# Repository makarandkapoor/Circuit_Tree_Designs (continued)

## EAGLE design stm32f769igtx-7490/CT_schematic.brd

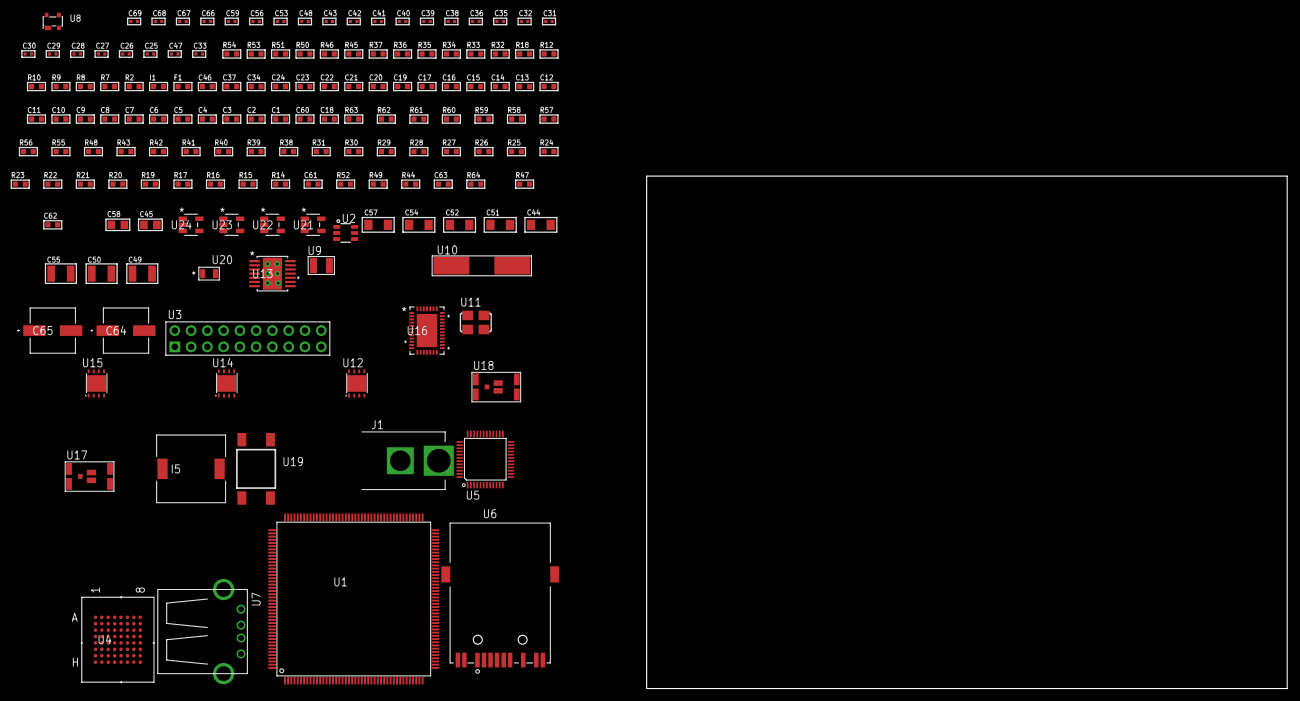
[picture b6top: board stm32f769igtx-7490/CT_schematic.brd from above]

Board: 2 copper layers, 100.0 x 80.0 mm, 154 parts (0 on the bottom side), 146 nets, no tracks yet.

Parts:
C1, C21, C34, C37, C46: 1e-06; C0603
C2, C3, C4, C5, C6, C7, C8, C9, C10, C11, C12, C13, C14, C15, C16, C17, C19, C22, C23, C24: 1e-07; C0603
C18: 4.7e-06; C0603
C20: 1e-08; C0603
C25, C26, C27, C28: 1e-11; C0402
C29, C30, C35, C38, C40, C41, C48, C59: 1e-07; C0402
C31, C32, C36, C39, C42, C43, C53, C56, C66, C67, C68, C69: 1e-08; C0402
C33: 2.2e-08; C0402
C44, C51, C52, C54, C57: 1e-05; C1206
C45, C58: 1e-05; C0805
C47: 3.3e-09; C0402
C49, C50: 2.2e-05; C1210
C55: 1e-05; C1210
C60: 2.2e-06; C0603
C61: 2.45e-08; R0603
C62: 2.8258362168397e-09; R0603
C63: 7.105e-09; R0603
C64, C65: 0.0001; EXV-9H
F1: 240.0; L0603
I1: 97.0; R0603
I5: 3.8e-06; DR1040
J1: PJ-037B; PJ-037B_PACKAGE
R2, R46, R51, R54: 1000.0; R0603
R7, R8, R9, R37: 4700.0; R0603
R10, R12: 2200.0; R0603
R14: 47000.0; R0603
R15, R16, R17, R19, R20, R21, R22, R23, R24, R25, R26, R27, R28, R29, R30, R31, R38, R39, R40, R41, R42, R43, R55, R57, R58, R61, R62, R63: 10000.0; R0603
R18: 1270.0; R0603
R32, R33: 0.1; R0603
R34, R35, R45, R53: 200.0; R0603
R36: 2490.0; R0603
R44, R49, R52: 100000.0; R0603
R47: 71007.101651032; R0603
R48: 22000.0; R0603
R50: 3900.0; R0603
R56: 75000.0; R0603
R59, R60: 95300.0; R0603
R64: 85527.272727273; R0603
U1: STM32F769IGT6; LQFP176
U2: MAX4995AAUT+T; SOT-23-6
U3: TST-110-05-T-D-RA
U4: mt28ew512aba1HPC-0AAT; LBGA-64
U5: RTL8201FL-VB-CG
U6: 7498011122R
U7: 61400416021; USB-A-H
U8: prtr5v0u2ax; SOT143B
U9: ABS07-32.768KHZ-7-T
U10: ABLS-25.000MHZ-B2F-T
U11: ASFL1-25MHZ-NCS; ASFL1
U12, U14, U15: LP3878SDX-ADJ/NOPB; WSON-8
U13: tps54325PWP; HTSSOP14
U16: LTC2928CUHF#PBF; QFN-38_UHF
U17, U18: IRF8306MTRPbF; IRF8306MTRPBF
U19: 4-1437565-2; SW_4-1437565-2
U20: Q65110A2395; LGM67K-G1J2-24-Z
U21, U22, U23, U24: nc7sz125m5x; NC7SZ125M5X

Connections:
CLK_CRYSTAL_U1_9: C25.1, U1.9, U9.1
CLK_CRYSTAL_U1_10: C26.1, U1.10, U9.2
CLK_CRYSTAL_U1_29: C27.1, U1.29, U10.1
CLK_CRYSTAL_U1_30: C28.1, U1.30, U10.2
CLK_U5_43: U5.43, U11.3
GND: C1.2, C2.2, C3.2, C4.2, C5.2, C6.2, C7.2, C8.2, C9.2, C10.2, C11.2, C12.2, C13.2, C14.2, C15.2, C16.2, C17.2, C18.2, C19.2, C20.2, C21.2, C22.2, C23.2, C24.2, C25.2, C26.2, C27.2, C28.2, C29.2, C30.2, C31.2, C32.2, C33.2, C34.2, C35.2, C36.2, C37.2, C38.2, C39.2, C40.2, C41.2, C42.2, C43.2, C44.2, C45.2, C46.2, C47.2, C49.2, C50.2, C51.2, C52.2, C53.2, C54.2, C55.2, C56.2, C57.2, C58.2, C59.2, C60.2, C61.2, C62.2, C63.2, C64.2, C65.2, C66.2, C67.2, C68.2, C69.2, J1.2, R2.2, R14.2, R15.2, R18.2, R20.2, R26.2, R32.2, R33.2, R36.2, R38.2, R40.2, R41.2, R42.2, R46.2, R48.2, R51.2, R54.2, R56.2, R59.2, R60.2, R61.2, R62.2, R63.2, U1.14, U1.22, U1.37, U1.61, U1.71, U1.95, U1.103, U1.109, U1.117, U1.130, U1.135, U1.148, U1.158, U2.2, U3.4, U3.6, U3.8, U3.10, U3.12, U3.14, U3.16, U3.18, U3.20, U4.E8, U4.H2, U4.H7, U5.7, U5.20, U5.33, U5.42, U5.47, U6.11, U7.4, U7.5, U7.6, U8.1, U11.2, U12.3, U12.PAD, U13.5, U13.8, U13.9, U13.15, U14.3, U14.PAD, U15.3, U15.PAD, U16.8, U16.9, U16.10, U16.12, U16.13, U16.24, U16.25, U16.30, U16.32, U16.39, U20.C, U21.2, U21.3, U22.1, U22.3, U23.1, U23.3, U24.1, U24.3
NET_U1_31: R9.1, U1.31, U24.4
NET_U1_33: R10.1, U1.33, U5.30
NET_U1_39: C20.1, C21.1, F1.1, U1.38, U1.39
NET_U1_42: R12.1, U1.42, U5.31
NET_U1_48: R17.1, U1.48
NET_U1_125: R18.1, U1.125
NET_U1_129: C24.1, U1.129
NET_U1_166: R15.1, U1.166
NET_U1_171: R16.1, U1.171
NET_U1_176: U19.3, U19.4
NET_U2_3: R14.1, U2.3
NET_U3_19: R26.1, U3.19
NET_U4_B4: R30.1, U4.B4
NET_U4_B5: R8.1, U4.B5, U23.4
NET_U5_6: C34.1, C35.1, C36.1, I1.1, U5.6, U5.41
NET_U5_10: R41.1, U5.10
NET_U5_29: R7.1, U5.29, U22.4
NET_U5_32: R37.1, U5.32
NET_U5_34: R39.1, U5.34
NET_U5_35: R40.1, U5.35
NET_U5_40: C41.1, U5.40
NET_U5_46: R36.1, U5.46
NET_U5_48: C40.1, U5.48
NET_U6_1: U5.1, U6.1
NET_U6_3: U5.2, U6.3
NET_U6_4: U5.4, U6.4
NET_U6_5: C33.1, U6.2, U6.5
NET_U6_6: U5.5, U6.6
NET_U6_8: R33.1, U6.8
NET_U6_10: R34.1, U6.10
NET_U6_12: R35.1, U6.12
NET_U6_13: R32.1, U6.13, U6.14
NET_U12_1: C43.1, U12.1
NET_U12_6: R45.2, R46.1, U12.6
NET_U12_8: R44.1, U12.8
NET_U13_2: R47.2, R48.1, U13.2
NET_U13_3: C46.1, U13.3
NET_U13_4: C47.1, U13.4
NET_U13_10: C48.1, I5.1, U13.10, U13.11
NET_U13_12: C48.2, U13.12
NET_U14_1: C53.1, U14.1
NET_U14_6: R50.2, R51.1, U14.6
NET_U14_8: R49.1, U14.8
NET_U15_1: C56.1, U15.1
NET_U15_6: R53.2, R54.1, U15.6
NET_U15_8: R52.1, U15.8
NET_U16_3: R62.1, U16.3
NET_U16_6: R59.1, U16.6
NET_U16_7: R60.1, U16.7
NET_U16_16: R61.1, R64.1, U16.16
NET_U16_18: R58.1, U16.18
NET_U16_19: R57.1, U16.19, U16.20
NET_U16_21: R55.1, R56.1, U16.21, U21.4, U22.2, U23.2, U24.2
NET_U16_22: C59.1, R55.2, R57.2, R58.2, U16.11, U16.22
NET_U16_26: C62.1, U16.26
NET_U16_27: C61.1, U16.27
NET_U16_28: C63.1, U16.28
NET_U16_38: R63.1, U16.38
NET_U17_3: U16.2, U17.3
NET_U18_3: U16.37, U18.3
NET_U19_1: R2.1, U19.1, U19.2
PROC_ETH_COL: U1.44, U5.38
PROC_ETH_CRS: U1.43, U5.36
PROC_ETH_RXD0: U1.54, U5.14
PROC_ETH_RXD1: U1.55, U5.16
PROC_ETH_RXD2: U1.56, U5.17
PROC_ETH_RXD3: R42.1, U1.57, U5.18
PROC_ETH_RX_CLK: U1.41, U5.19
PROC_ETH_RX_DV: R38.1, U1.53, U5.13
PROC_ETH_RX_ER: R43.1, U1.12, U5.39
PROC_ETH_TXD0: U1.85, U5.23
PROC_ETH_TXD1: U1.86, U5.24
PROC_ETH_TXD2: U1.34, U5.25
PROC_ETH_TXD3: U1.167, U5.26
PROC_ETH_TX_CLK: U1.35, U5.22
PROC_ETH_TX_EN: U1.80, U5.27
PROC_FMC_A0: U1.16, U4.E2
PROC_FMC_A1: U1.17, U4.D2
PROC_FMC_A2: U1.18, U4.C2
PROC_FMC_A3: U1.19, U4.A2
PROC_FMC_A4: U1.20, U4.B2
PROC_FMC_A5: U1.21, U4.D3
PROC_FMC_A6: U1.60, U4.C3
PROC_FMC_A7: U1.63, U4.A3
PROC_FMC_A8: U1.64, U4.B6
PROC_FMC_A9: U1.65, U4.A6
PROC_FMC_A10: U1.66, U4.C6
PROC_FMC_A11: U1.67, U4.D6
PROC_FMC_A12: U1.110, U4.B7
PROC_FMC_A13: U1.111, U4.A7
PROC_FMC_A14: U1.112, U4.C7
PROC_FMC_A15: U1.113, U4.D7
PROC_FMC_A16: U1.92, U4.E7
PROC_FMC_A17: U1.93, U4.B3
PROC_FMC_A18: U1.94, U4.C4
PROC_FMC_A19: U1.2, U4.D5
PROC_FMC_A20: U1.3, U4.D4
PROC_FMC_A21: U1.4, U4.C5
PROC_FMC_A22: U1.5, U4.B8
PROC_FMC_A23: U1.1, U4.C8
PROC_FMC_A24: U1.156, U4.F8
PROC_FMC_D0: U1.97, U4.E3
PROC_FMC_D1: U1.98, U4.H3
PROC_FMC_D2: U1.142, U4.E4
PROC_FMC_D3: U1.143, U4.H4
PROC_FMC_D4: U1.68, U4.H5
PROC_FMC_D5: U1.69, U4.E5
PROC_FMC_D6: U1.70, U4.H6
PROC_FMC_D7: U1.73, U4.E6
PROC_FMC_D8: U1.74, U4.F3
PROC_FMC_D9: U1.75, U4.G3
PROC_FMC_D10: U1.76, U4.F4
PROC_FMC_D11: U1.77, U4.G4
PROC_FMC_D12: U1.78, U4.F5
PROC_FMC_D13: U1.89, U4.G6
PROC_FMC_D14: U1.90, U4.F6
PROC_FMC_D15: U1.91, U4.G7
PROC_FMC_INT: U1.115, U4.A4
PROC_FMC_NBL0: R31.1, U1.169, U4.F7
PROC_FMC_NE2: R27.1, U1.121, U4.F2
PROC_FMC_NOE: R28.1, U1.146, U4.G2
PROC_FMC_NWE: R29.1, U1.147, U4.A5
PROC_GPIO_TO_U1_USB_FAULT: R19.1, U1.8, U2.6
PROC_GPIO_TO_U1_VBUS_EN: R20.1, U1.7, U2.4
PROC_SYS_JTCK_SWCLK: R24.1, U1.137, U3.9
PROC_SYS_JTDI: R22.1, U1.138, U3.5
PROC_SYS_JTDO_SWO: U1.161, U3.13
PROC_SYS_JTMS_SWDIO: R23.1, U1.128, U3.7
PROC_SYS_JTRST: R21.1, U1.162, U3.3
PROC_USB_OTG_FS_DM: U1.126, U7.2, U8.3
PROC_USB_OTG_FS_DP: U1.127, U7.3, U8.2
PROC_USB_OTG_FS_VBUS: U1.124, U2.1, U7.1, U8.4
RST_OUT_U3_SRESET_B: R25.1, U3.15, U21.1
VCC_10V7: C60.1, C64.1, C65.1, J1.1, R64.2, U16.23, U17.1, U17.2, U17.6, U17.7, U18.1, U18.2, U18.6, U18.7
VCC_S1_10V7: C44.1, C51.1, C52.1, C54.1, R44.2, R49.2, U12.4, U13.7, U13.13, U13.14, U14.4, U17.4, U17.5
VCC_S2_10V7: C57.1, R52.2, U15.4, U18.4, U18.5
VCC_TIER1_1V2: C23.1, C45.1, R45.1, U1.81, U12.5
VCC_TIER1_3V3: C1.1, C2.1, C3.1, C4.1, C5.1, C6.1, C7.1, C8.1, C9.1, C10.1, C11.1, C12.1, C13.1, C14.1, C15.1, C16.1, C17.1, C18.1, C19.1, C22.1, C29.1, C30.1, C31.1, C32.1, C37.1, C38.1, C39.1, C42.1, C49.1, C50.1, C66.1, C67.1, C68.1, C69.1, F1.2, I1.2, I5.2, R7.2, R8.2, R9.2, R10.2, R12.2, R16.2, R17.2, R19.2, R21.2, R22.2, R23.2, R24.2, R25.2, R27.2, R28.2, R29.2, R30.2, R31.2, R37.2, R39.2, R43.2, R47.1, U1.6, U1.15, U1.23, U1.36, U1.49, U1.62, U1.72, U1.82, U1.96, U1.99, U1.118, U1.131, U1.136, U1.149, U1.159, U1.172, U3.1, U3.2, U4.D8, U4.F1, U4.G5, U5.15, U5.21, U5.37, U11.4, U13.1, U21.5, U22.5, U23.5, U24.5
VCC_TIER1_5V0: C55.1, R50.1, U2.5, U14.5
VCC_TIER2_1V2: C58.1, R53.1, U15.5

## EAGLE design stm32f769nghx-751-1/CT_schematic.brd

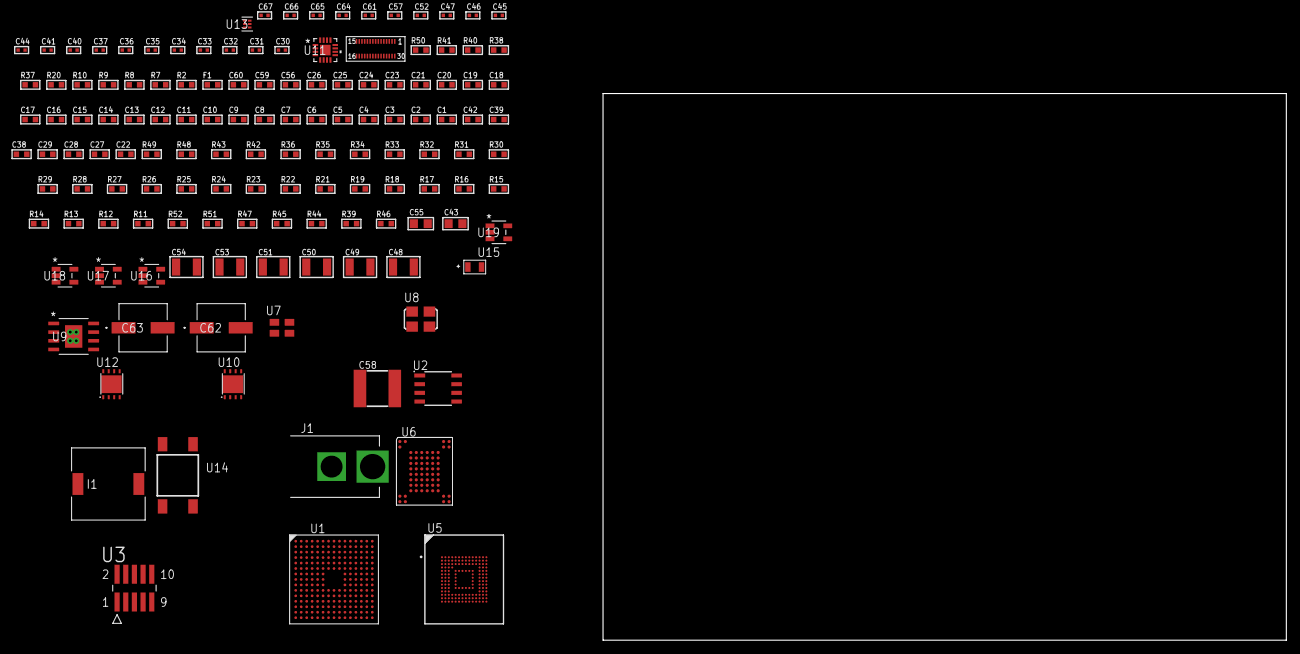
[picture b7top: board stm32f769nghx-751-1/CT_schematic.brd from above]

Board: 2 copper layers, 100.0 x 80.0 mm, 136 parts (0 on the bottom side), 79 nets, no tracks yet.

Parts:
C1, C25, C56: 1e-06; C0603
C2, C3, C4, C5, C6, C7, C8, C9, C10, C11, C12, C13, C14, C15, C16, C17, C18, C19, C20, C21, C23, C26: 1e-07; C0603
C22: 4.7e-06; C0603
C24: 1e-08; C0603
C27, C28, C29, C38, C39, C42: 2.2e-06; C0603
C30, C46, C47, C52, C64, C65, C66, C67: 1e-08; C0402
C31, C32, C33, C34, C35, C36, C37, C40, C41, C44, C45, C57, C61: 1e-07; C0402
C43, C55: 1e-05; C0805
C48, C49, C50, C51, C53, C54: 1e-05; C1210
C58: 6.8e-05; 2220
C59: 8e-07; R0603
C60: 8e-06; R0603
C62, C63: 0.0001; EXV-9H
F1: 240.0; L0603
I1: 5.2e-06; DR1040
J1: PJ-037B; PJ-037B_PACKAGE
R2, R41: 1000.0; R0603
R7, R8, R9: 4700.0; R0603
R10, R38: 2200.0; R0603
R11, R12, R13, R14, R15, R16, R17, R18, R19, R21, R32, R33, R34, R35, R36, R48, R49: 10000.0; R0603
R20: 5.0; R0603
R22, R23, R24, R25, R26, R27, R28, R29, R30, R31: 34000.0; R0603
R37: 910.0; R0603
R39, R45, R47: 100000.0; R0603
R40: 1800.0; R0603
R42: 20000.0; R0603
R43: 91000.0; R0603
R44: 300000.0; R0603
R46: 842943.08; R0603
R50: 9100.0; R0603
R51: 680000.0; R0603
R52: 120000.0; R0603
U1: STM32F769NGH6; TFBGA216
U2: AT25M02-SSHD-T; SOIC-8
U3: FTSH-105-01-L-DV-K; SAMTEC_FTSH-105-01-L-DV-K
U4: LH430WV2-SD01
U5: mtfc4gmcdm; TFBGA-153
U6: TH58NVG3S0HBAI4
U7: ASEK-32.768KHz-ECST; ASEK
U8: ASFL1-25MHZ-NCS; ASFL1
U9: MIC5234YME; SOIC-8_EP
U10: LP3878SDX-ADJ/NOPB; WSON-8
U11: LTC3601EUD#PBF; QFN-16_EP
U12: LP2951ACSDX/NOPB; WSON-8
U13: TPS3895ADRYR; SON-6
U14: 4-1437565-2; SW_4-1437565-2
U15: Q65110A2395; LGM67K-G1J2-24-Z
U16, U17, U18, U19: nc7sz125m5x; NC7SZ125M5X

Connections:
CLK_U1_E1: U1.E1, U7.3
CLK_U1_G1: U1.G1, U8.3
GND: C1.2, C2.2, C3.2, C4.2, C5.2, C6.2, C7.2, C8.2, C9.2, C10.2, C11.2, C12.2, C13.2, C14.2, C15.2, C16.2, C17.2, C18.2, C19.2, C20.2, C21.2, C22.2, C23.2, C24.2, C25.2, C26.2, C27.2, C28.2, C29.2, C30.2, C31.2, C32.2, C33.2, C34.2, C35.2, C36.2, C37.2, C38.2, C39.2, C40.2, C41.2, C42.2, C43.2, C44.2, C45.2, C46.2, C47.2, C48.2, C49.2, C50.2, C51.2, C52.2, C53.2, C54.2, C55.2, C56.2, C58.1, C58.2, C59.2, C60.2, C61.2, C62.2, C63.2, C64.2, C65.2, C66.2, C67.2, J1.2, R2.2, R11.2, R13.2, R20.2, R21.2, R38.2, R41.2, R42.2, R44.2, R47.2, R50.2, R52.2, U1.F2, U1.F6, U1.F7, U1.F8, U1.F9, U1.F10, U1.G6, U1.G10, U1.G12, U1.H6, U1.H10, U1.J6, U1.J10, U1.K6, U1.K7, U1.K8, U1.K9, U1.K10, U1.L6, U1.M1, U1.N1, U2.4, U3.3, U3.5, U4.1, U4.6, U4.9, U4.12, U4.15, U4.17, U4.18, U4.19, U4.24, U4.27, U5.C4, U5.E7, U5.G5, U5.H10, U5.K8, U5.N2, U5.N5, U5.P4, U5.P6, U6.C5, U6.K3, U6.K8, U7.2, U8.2, U9.7, U9.EPAD, U10.3, U10.PAD, U11.1, U11.9, U11.17, U12.3, U12.4, U12.PAD, U13.2, U15.C, U16.2, U16.3, U17.1, U17.3, U18.1, U18.3, U19.1, U19.3
NET_U1_E5: R12.1, U1.E5
NET_U1_E6: R11.1, U1.E6
NET_U1_E11: C29.1, U1.E11
NET_U1_G13: C27.1, U1.G13, U1.K12
NET_U1_J1: R9.1, U1.J1, U19.4
NET_U1_L5: R13.1, U1.L5
NET_U1_L11: C28.1, U1.L11
NET_U1_R1: C24.1, C25.1, F1.1, U1.P1, U1.R1
NET_U1_R15: U14.3, U14.4
NET_U2_3: R14.1, U2.3
NET_U2_7: R16.1, U2.7
NET_U3_9: R20.1, U3.9
NET_U4_4: R7.1, U4.4, U17.4
NET_U4_20: R21.1, U4.20
NET_U5_C2: C39.1, C40.1, U5.C2
NET_U5_K5: R8.1, U5.K5, U18.4
NET_U6_C3: R35.1, U6.C3
NET_U9_4: R37.2, R38.1, U9.4
NET_U10_1: C52.1, U10.1
NET_U10_6: R40.2, R41.1, U10.6
NET_U10_8: R39.1, U10.8
NET_U11_3: C57.2, I1.1, U11.3, U11.4
NET_U11_6: C57.1, U11.6
NET_U11_7: C56.1, U11.7, U11.12
NET_U11_10: R44.1, U11.10
NET_U11_11: R42.1, R43.1, U11.11
NET_U11_ATNET_3: I1.2, R43.2
NET_U12_5: R45.1, U12.5
NET_U12_7: R46.2, R47.1, U12.7
NET_U13_1: R49.1, R50.1, U13.1
NET_U13_3: R51.2, R52.1, U13.3
NET_U13_4: R48.1, U13.4, U16.4, U17.2, U18.2, U19.2
NET_U14_1: R2.1, U14.1, U14.2
PROC_DSIHOST_CKN: U1.H13, U4.13
PROC_DSIHOST_CKP: U1.H12, U4.14
PROC_DSIHOST_D0N: U1.J13, U4.7
PROC_DSIHOST_D0P: U1.J12, U4.8
PROC_DSIHOST_D1N: U1.F13, U4.10
PROC_DSIHOST_D1P: U1.F12, U4.11
PROC_FMC_A16: U1.N10, U6.D5
PROC_FMC_A17: U1.M10, U6.C4
PROC_FMC_D0: U1.L12, U6.H4
PROC_FMC_D1: U1.K13, U6.J4
PROC_FMC_D2: U1.B12, U6.K4
PROC_FMC_D3: U1.C12, U6.K5
PROC_FMC_D4: U1.R8, U6.K6
PROC_FMC_D5: U1.N9, U6.J7
PROC_FMC_D6: U1.P9, U6.K7
PROC_FMC_D7: U1.R9, U6.J8
PROC_FMC_INT: R36.1, U1.J14, U6.C8
PROC_FMC_NCE: R32.1, U1.D9, U6.C6
PROC_FMC_NOE: R33.1, U1.D11, U6.D4
PROC_FMC_NWE: R34.1, U1.C10, U6.C7
PROC_SDMMC1_CK: R31.1, U1.A12, U5.M6
PROC_SDMMC1_CMD: R30.1, U1.D12, U5.M5
PROC_SDMMC1_D0: R22.1, U1.G14, U5.A3
PROC_SDMMC1_D1: R23.1, U1.F14, U5.A4
PROC_SDMMC1_D2: R24.1, U1.B14, U5.A5
PROC_SDMMC1_D3: R25.1, U1.B13, U5.B2
PROC_SDMMC1_D4: R26.1, U1.A7, U5.B3
PROC_SDMMC1_D5: R27.1, U1.B4, U5.B4
PROC_SDMMC1_D6: R28.1, U1.H15, U5.B5
PROC_SDMMC1_D7: R29.1, U1.G15, U5.B6
PROC_SPI1_MISO: U1.A9, U2.2
PROC_SPI1_MOSI: U1.A8, U2.5
PROC_SPI1_NSS: R15.1, U1.A13, U2.1
PROC_SPI1_SCK: U1.B8, U2.6
PROC_SYS_JTCK_SWCLK: R18.1, U1.A14, U3.4
PROC_SYS_JTDO_SWO: U1.A10, U3.6
PROC_SYS_JTMS_SWDIO: R19.1, U1.A15, U3.2
RST_OUT_U3_JTAG_RST_B: R17.1, U3.10, U16.1
VCC_S1_13V7: C48.1, C49.1, C53.1, C55.1, C59.1, C62.1, C63.1, J1.1, R39.2, U9.5, U9.8, U10.4, U11.15, U11.16, U12.8
VCC_TIER1_1V5: C50.1, C51.1, R37.1, U4.29, U9.1
VCC_TIER1_2V8: C34.1, C35.1, C36.1, C54.1, R40.1, U4.16, U4.21, U4.22, U4.23, U10.5
VCC_TIER1_3V3: C1.1, C2.1, C3.1, C4.1, C5.1, C6.1, C7.1, C8.1, C9.1, C10.1, C11.1, C12.1, C13.1, C14.1, C15.1, C16.1, C17.1, C18.1, C19.1, C20.1, C21.1, C22.1, C23.1, C26.1, C30.1, C31.1, C32.1, C37.1, C38.1, C41.1, C42.1, C43.1, C44.1, C45.1, C46.1, C47.1, C58.2, C61.1, C64.1, C65.1, C66.1, C67.1, F1.2, I1.2, R7.2, R8.2, R9.2, R10.2, R12.2, R14.2, R15.2, R16.2, R17.2, R18.2, R19.2, R22.2, R23.2, R24.2, R25.2, R26.2, R27.2, R28.2, R29.2, R30.2, R31.2, R32.2, R33.2, R34.2, R35.2, R36.2, R43.2, R48.2, R49.2, R51.1, U1.C1, U1.E7, U1.E8, U1.E9, U1.E10, U1.F4, U1.F5, U1.F11, U1.G5, U1.G11, U1.H5, U1.H11, U1.J5, U1.J11, U1.K5, U1.K11, U1.L7, U1.L8, U1.L9, U1.L10, U2.8, U3.1, U4.2, U5.C6, U5.E6, U5.F5, U5.J10, U5.K9, U5.M4, U5.N4, U5.P3, U5.P5, U6.H8, U6.J6, U7.4, U8.4, U11.8, U13.6, U16.5, U17.5, U18.5, U19.5
VCC_TIER1_12V0: C33.1, C60.1, R45.2, R46.1, U4.30, U12.1

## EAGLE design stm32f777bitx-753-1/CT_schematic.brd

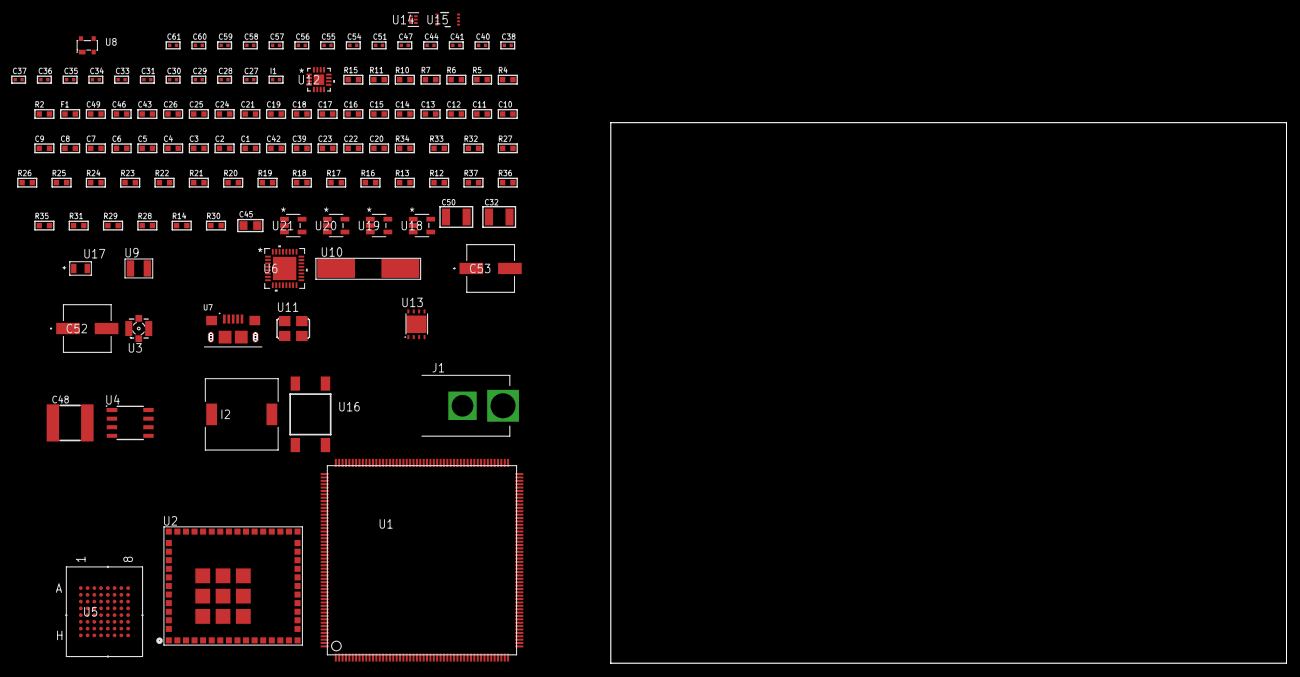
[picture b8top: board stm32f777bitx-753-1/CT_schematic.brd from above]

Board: 2 copper layers, 119 parts (0 on the bottom side), 108 nets, no tracks yet.

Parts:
C1, C25, C43, C46: 1e-06; C0603
C2, C3, C4, C5, C6, C7, C8, C9, C10, C11, C12, C13, C14, C15, C16, C17, C18, C19, C21, C26: 1e-07; C0603
C20: 4.7e-06; C0603
C22, C23, C39, C42: 2.2e-06; C0603
C24: 1e-08; C0603
C27, C28, C29, C30: 1e-11; C0402
C31: 1e-12; C0402
C32: 2.2e-05; C1210
C33, C34, C38, C40, C41, C47, C51, C55, C57: 1e-07; C0402
C35, C36, C37, C44, C54, C56, C58, C59, C60, C61: 1e-08; C0402
C45: 1e-05; C0805
C48: 6.8e-05; 2220
C49: 8e-07; R0603
C50: 1e-05; C1210
C52, C53: 0.0001; EXV-9H
F1: 240.0; L0603
I1: 3.6e-09; C0402
I2: 3.8e-06; DR1040
J1: PJ-037B; PJ-037B_PACKAGE
R2: 1000.0; R0603
R4, R5, R6, R7: 4700.0; R0603
R10, R11: 2200.0; R0603
R12, R13, R16, R17, R18, R19, R20, R21, R22, R23, R24, R25, R32, R33: 10000.0; R0603
R14, R29, R31: 100000.0; R0603
R15: 2700.0; R0603
R26: 20000.0; R0603
R27: 39000.0; R0603
R28, R35: 300000.0; R0603
R30: 153694.38; R0603
R34: 82000.0; R0603
R36: 120000.0; R0603
R37: 200000.0; R0603
U1: STM32F777BIT6; LQFP208
U2: CC3200MODR1M2AMOBT; LGA63S127P16X13_2050X1750X150
U3: 73412-0114; COAXIAL_C
U4: 24AA1025T-I/SN; SOIC-8
U5: mt28ew512aba1HPC-0AAT; LBGA-64
U6: TUSB1210BRHBR; RHB32_3P45X3P45
U7: 10118193-0001LF; FCI_10118193-0001LF
U8: prtr5v0u2ax; SOT143B
U9: ABS07-32.768KHZ-7-T
U10: ABLS-25.000MHZ-B2F-T
U11: ASFL1-19.2MHZ-NCS; ASFL1
U12: LTC3601EUD#PBF; QFN-16_EP
U13: LP2951ACSDX/NOPB; WSON-8
U14: TPS3895ADRYR; SON-6
U15: LSF0102DCTR; DCU0008A_N
U16: 4-1437565-2; SW_4-1437565-2
U17: Q65110A2395; LGM67K-G1J2-24-Z
U18, U19, U20, U21: nc7sz125m5x; NC7SZ125M5X

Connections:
CLK_CRYSTAL_U1_9: C27.1, U1.9, U9.1
CLK_CRYSTAL_U1_10: C28.1, U1.10, U9.2
CLK_CRYSTAL_U1_32: C29.1, U1.32, U10.1
CLK_CRYSTAL_U1_33: C30.1, U1.33, U10.2
CLK_U6_1: U6.1, U11.3
GND: C1.2, C2.2, C3.2, C4.2, C5.2, C6.2, C7.2, C8.2, C9.2, C10.2, C11.2, C12.2, C13.2, C14.2, C15.2, C16.2, C17.2, C18.2, C19.2, C20.2, C21.2, C22.2, C23.2, C24.2, C25.2, C26.2, C27.2, C28.2, C29.2, C30.2, C31.2, C32.2, C33.2, C34.2, C35.2, C36.2, C37.2, C38.2, C39.2, C40.2, C41.2, C42.2, C43.2, C44.2, C45.2, C46.2, C48.1, C48.2, C49.2, C50.2, C51.2, C52.2, C53.2, C54.2, C55.2, C56.2, C57.2, C58.2, C59.2, C60.2, C61.2, J1.2, R2.2, R12.2, R14.2, R15.2, R25.2, R26.2, R28.2, R31.2, R34.2, R36.2, U1.14, U1.25, U1.40, U1.51, U1.60, U1.72, U1.82, U1.93, U1.114, U1.125, U1.136, U1.149, U1.170, U1.184, U1.202, U2.1, U2.2, U2.16, U2.27, U2.28, U2.30, U2.32, U2.38, U2.43, U2.55, U2.56, U2.57, U2.58, U2.59, U2.60, U2.61, U2.62, U2.63, U3.1, U3.2, U3.3, U3.4, U4.4, U4.7, U5.E8, U5.H2, U5.H7, U6.33, U7.5, U7.6, U7.7, U7.8, U7.9, U8.1, U11.2, U12.1, U12.9, U12.17, U13.3, U13.4, U13.PAD, U14.2, U15.1, U17.C, U18.1, U18.3, U19.1, U19.3, U20.1, U20.3, U21.1, U21.3
NET_U1_34: R6.1, U1.34, U20.4
NET_U1_42: C24.1, C25.1, F1.1, U1.41, U1.42
NET_U1_48: R10.1, U1.48, U4.6
NET_U1_49: R11.1, U1.49, U4.5
NET_U1_92: C22.1, U1.92
NET_U1_148: C23.1, U1.148
NET_U1_197: R12.1, U1.197
NET_U1_203: R13.1, U1.203
NET_U1_208: U16.3, U16.4
NET_U2_21: R14.1, U2.21
NET_U2_23: R15.1, U2.23
NET_U2_35: R5.1, U2.35, U19.4
NET_U3_1: C31.1, I1.1, U3.1
NET_U4_1: R17.1, U4.1
NET_U4_2: R18.1, U4.2
NET_U4_3: R16.1, U4.3
NET_U5_B4: R22.1, U5.B4
NET_U5_B5: R4.1, U5.B5, U18.4
NET_U6_11: R24.1, U6.11
NET_U6_12: C42.1, U6.12
NET_U6_14: R25.1, U6.14
NET_U6_20: C39.1, U6.20
NET_U6_27: R7.1, U6.27, U21.4
NET_U7_1: C43.1, U6.22, U7.1, U8.4
NET_U7_2: U6.19, U7.2, U8.3
NET_U7_3: U6.18, U7.3, U8.2
NET_U12_3: C47.2, I2.1, U12.3, U12.4
NET_U12_6: C47.1, U12.6
NET_U12_7: C46.1, U12.7, U12.12
NET_U12_10: R28.1, U12.10
NET_U12_11: R26.1, R27.1, U12.11
NET_U12_ATNET_3: I2.2, R27.2
NET_U13_5: R29.1, U13.5
NET_U13_7: R30.2, R31.1, U13.7
NET_U14_1: R33.1, R34.1, U14.1
NET_U14_3: R35.2, R36.1, U14.3
NET_U14_4: R32.1, U14.4, U18.2, U19.2, U20.2, U21.2
NET_U15_8: R37.1, U15.8
NET_U16_1: R2.1, U16.1, U16.2
PROC_FMC_A0: U1.16, U5.E2
PROC_FMC_A1: U1.17, U5.D2
PROC_FMC_A2: U1.18, U5.C2
PROC_FMC_A3: U1.22, U5.A2
PROC_FMC_A4: U1.23, U5.B2
PROC_FMC_A5: U1.24, U5.D3
PROC_FMC_A6: U1.71, U5.C3
PROC_FMC_A7: U1.74, U5.A3
PROC_FMC_A8: U1.75, U5.B6
PROC_FMC_A9: U1.76, U5.A6
PROC_FMC_A10: U1.77, U5.C6
PROC_FMC_A11: U1.78, U5.D6
PROC_FMC_A12: U1.129, U5.B7
PROC_FMC_A13: U1.130, U5.A7
PROC_FMC_A14: U1.131, U5.C7
PROC_FMC_A15: U1.132, U5.D7
PROC_FMC_A16: U1.111, U5.E7
PROC_FMC_A17: U1.112, U5.B3
PROC_FMC_A18: U1.113, U5.C4
PROC_FMC_A19: U1.2, U5.D5
PROC_FMC_A20: U1.3, U5.D4
PROC_FMC_A21: U1.4, U5.C5
PROC_FMC_A22: U1.5, U5.B8
PROC_FMC_A23: U1.1, U5.C8
PROC_FMC_A24: U1.182, U5.F8
PROC_FMC_D0: U1.116, U5.E3
PROC_FMC_D1: U1.117, U5.H3
PROC_FMC_D2: U1.164, U5.E4
PROC_FMC_D3: U1.165, U5.H4
PROC_FMC_D4: U1.79, U5.H5
PROC_FMC_D5: U1.80, U5.E5
PROC_FMC_D6: U1.81, U5.H6
PROC_FMC_D7: U1.84, U5.E6
PROC_FMC_D8: U1.85, U5.F3
PROC_FMC_D9: U1.86, U5.G3
PROC_FMC_D10: U1.87, U5.F4
PROC_FMC_D11: U1.88, U5.G4
PROC_FMC_D12: U1.89, U5.F5
PROC_FMC_D13: U1.108, U5.G6
PROC_FMC_D14: U1.109, U5.F6
PROC_FMC_D15: U1.110, U5.G7
PROC_FMC_NBL0: R23.1, U1.200, U5.F7
PROC_FMC_NE2: R19.1, U1.140, U5.F2
PROC_FMC_NOE: R20.1, U1.168, U5.G2
PROC_FMC_NWAIT: U1.138, U5.A4
PROC_FMC_NWE: R21.1, U1.169, U5.A5
PROC_I2C1_SCL_TOXCVR: U2.3, U15.5
PROC_I2C1_SDA_TOXCVR: U2.4, U15.6
PROC_USB_OTG_HS_ULPI_CK: U1.54, U6.26
PROC_USB_OTG_HS_ULPI_D0: U1.50, U6.3
PROC_USB_OTG_HS_ULPI_D1: U1.61, U6.4
PROC_USB_OTG_HS_ULPI_D2: U1.62, U6.5
PROC_USB_OTG_HS_ULPI_D3: U1.90, U6.6
PROC_USB_OTG_HS_ULPI_D4: U1.91, U6.7
PROC_USB_OTG_HS_ULPI_D5: U1.104, U6.9
PROC_USB_OTG_HS_ULPI_D6: U1.105, U6.10
PROC_USB_OTG_HS_ULPI_D7: U1.194, U6.13
PROC_USB_OTG_HS_ULPI_DIR: U1.13, U6.31
PROC_USB_OTG_HS_ULPI_NXT: U1.38, U6.2
PROC_USB_OTG_HS_ULPI_STP: U1.35, U6.29
VCC_S1_11V6: C45.1, C49.1, C52.1, C53.1, J1.1, U12.15, U12.16, U13.8
VCC_TIER1_1V8: C1.1, C2.1, C3.1, C4.1, C5.1, C6.1, C7.1, C8.1, C9.1, C10.1, C11.1, C12.1, C13.1, C14.1, C15.1, C16.1, C17.1, C18.1, C19.1, C20.1, C21.1, C35.1, C36.1, C40.1, C41.1, C48.2, C51.1, C56.1, C57.1, C58.1, C59.1, C60.1, C61.1, F1.2, I2.2, R4.2, R6.2, R7.2, R10.2, R11.2, R13.2, R16.2, R17.2, R18.2, R19.2, R20.2, R21.2, R22.2, R23.2, R24.2, R27.2, R32.2, R33.2, R35.1, U1.6, U1.15, U1.26, U1.39, U1.52, U1.59, U1.73, U1.83, U1.94, U1.103, U1.115, U1.124, U1.150, U1.158, U1.171, U1.185, U1.204, U4.8, U5.D8, U5.F1, U6.28, U6.30, U6.32, U12.8, U14.6, U15.2, U18.5, U19.5, U20.5, U21.5
VCC_TIER1_3V3: C26.1, C32.1, C33.1, C34.1, C37.1, C38.1, C44.1, C50.1, C54.1, C55.1, R5.2, R29.2, R30.1, R37.2, U1.137, U2.36, U2.37, U2.40, U5.G5, U6.21, U11.4, U13.1, U15.7
